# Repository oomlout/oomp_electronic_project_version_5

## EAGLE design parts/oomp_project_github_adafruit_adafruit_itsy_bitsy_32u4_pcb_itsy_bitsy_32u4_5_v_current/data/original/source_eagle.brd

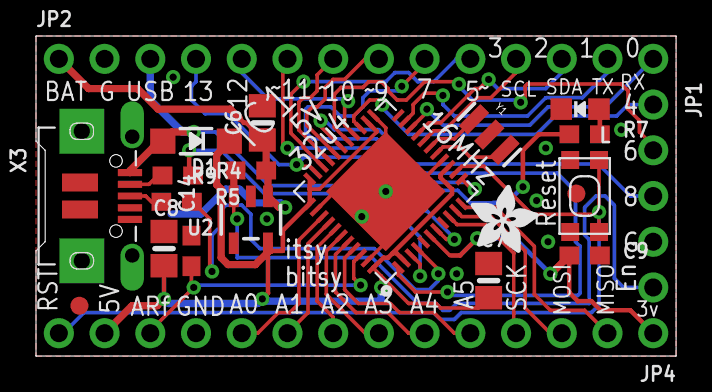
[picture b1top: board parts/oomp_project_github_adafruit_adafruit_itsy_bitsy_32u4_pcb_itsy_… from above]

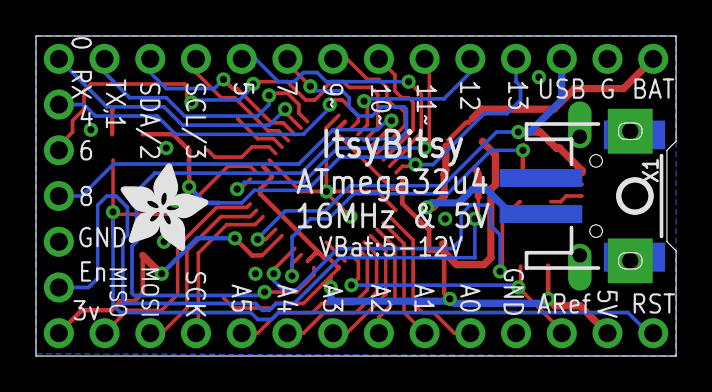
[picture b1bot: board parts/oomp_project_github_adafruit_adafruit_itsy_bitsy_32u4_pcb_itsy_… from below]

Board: 2 copper layers, 35.6 x 17.8 mm, 25 parts (3 on the bottom side), 38 nets.

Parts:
C6, C8: 10µF; 0805-NO
C7: 10uF; 0805-NO
C9, C14: 1uF; 0603-NO
D1: MBR120; SOD-123
IC1: ATMEGA32U4-MU; TQFN44_7MM
JP1: 1X05_ROUND
JP2, JP4: 1X14_ROUND70
L: RED; CHIPLED_0805_NOOUTLINE
R4, R5: 22; 0603-NO
R7: 2.2K; 0603-NO
R9: 100k; 0603-NO
SW1: SPST_TACT-KMR2; KMR2
U2: MIC5225-5.0; SOT23-5
U$4: ADAFRUIT_5MM
U$7: ADAFRUIT_3.5MM
U$10: PCBFEAT-REV-040
U$34, U$35: FIDUCIAL""; FIDUCIAL_1MM
X1: JSTPH2
X3: microUSB; 4UCONN_20329_V2
Y1: 16MHz; RESONATOR-SMD

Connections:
3.3V: C9.1, IC1.6, JP4.1
+5V: C7.1, C8.1, D1.C, IC1.2, IC1.14, IC1.24, IC1.33, IC1.34, IC1.44, JP4.13, U2.5
A0: IC1.36, JP4.10
A1: IC1.37, JP4.9
A2: IC1.38, JP4.8
A3: IC1.39, JP4.7
A4: IC1.40, JP4.6
A5: IC1.41, JP4.5
AREF: C14.1, IC1.42, JP4.12
D0: IC1.20, JP2.14
D1: IC1.21, JP2.13
D4: IC1.25, JP1.1
D5: IC1.31, JP2.10
D6: IC1.27, JP1.2
D7: IC1.1, JP2.9
D8: IC1.28, JP1.3
D9: IC1.29, JP2.8
D10: IC1.30, JP2.7
D11: IC1.12, JP2.6
D12: IC1.26, JP2.5
D13: IC1.32, JP2.4, R7.1
D+: IC1.4, R5.2
D-: IC1.3, R4.2
EN: JP1.5, R9.2, U2.3
GND: C6.2, C7.2, C8.2, C9.2, C14.2, IC1.5, IC1.15, IC1.23, IC1.35, IC1.43, JP1.4, JP2.2, JP4.11, L.C, SW1.2, SW1.4, U2.2, X1.1, X3.BASE@1, X3.BASE@2, X3.GND, X3.SPRT@1, X3.SPRT@2, X3.SPRT@3, X3.SPRT@4, Y1.2
MISO: IC1.11, JP4.2
MOSI: IC1.10, JP4.3
unnamed: L.A, R7.2
unnamed: IC1.16, Y1.3
unnamed: IC1.17, Y1.1
unnamed: R5.1, X3.D+
unnamed: R4.1, X3.D-
RST: IC1.13, JP4.14, SW1.1, SW1.3
SCK: IC1.9, JP4.4
SCL: IC1.18, JP2.11
SDA: IC1.19, JP2.12
VBAT: C6.1, JP2.1, R9.1, U2.1, X1.2
VBUS: D1.A, IC1.7, JP2.3, X3.VBUS

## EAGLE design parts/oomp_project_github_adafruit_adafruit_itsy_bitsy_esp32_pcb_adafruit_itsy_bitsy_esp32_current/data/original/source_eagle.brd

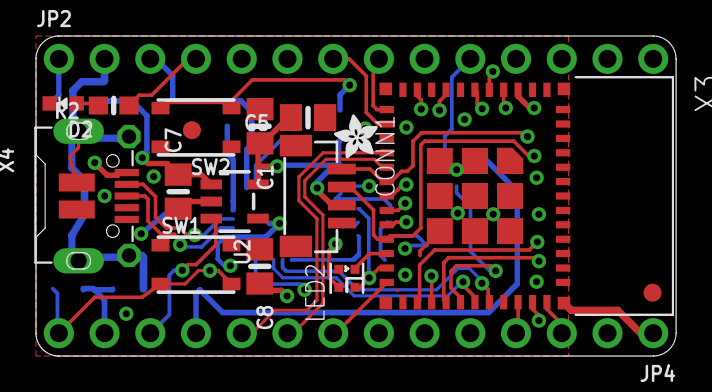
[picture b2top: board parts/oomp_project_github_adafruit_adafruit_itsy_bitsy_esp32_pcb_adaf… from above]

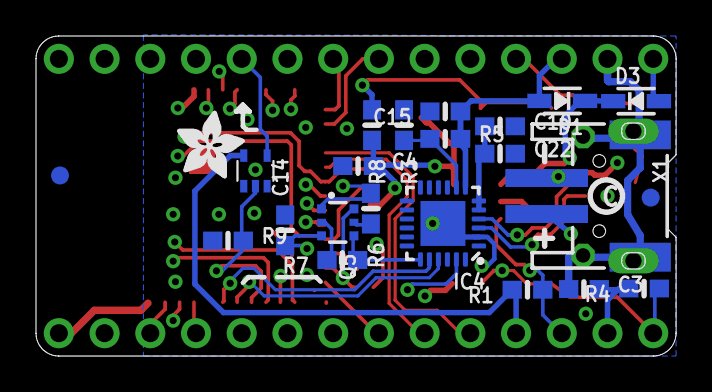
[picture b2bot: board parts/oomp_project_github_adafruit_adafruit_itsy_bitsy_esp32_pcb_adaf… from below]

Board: 4 copper layers, 35.6 x 17.8 mm, 87 parts (48 on the bottom side), 42 nets.

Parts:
C1, C5, C7, C8: 10uF; 0805-NO
C3, C4, C10, C14: 1uF; 0603-NO
C15, C22: 0.1uF; 0603-NO
CONN1: STEMMA_I2C_QTRA; JST_SH4_RA
D1, D3: BAT20J; SOD-323
D2: RED; CHIPLED_0603_NOOUTLINE
E$1: ADAFRUIT_2.5MM
E$2: ADAFRUIT_3.5MM
FID1, FID2, FID3, FID4: FIDUCIAL_1MM
IC1: 74AHCT1G125DCKR; SC70-5
IC4: CH9102F; QFN24_4MM_SMSC
JP2, JP4: 1X14_ROUND70
LED2: WS2812B_SK6805_1515; SK6805_1515
PLABEL0: PLABEL0
PLABEL1: PLABEL1
PLABEL2: PLABEL2
PLABEL3: PLABEL3
PLABEL4: PLABEL4
PLABEL5: PLABEL5
PLABEL6: PLABEL6
PLABEL7: PLABEL7
PLABEL8: PLABEL8
PLABEL9: PLABEL9
PLABEL10: PLABEL10
PLABEL11: PLABEL11
PLABEL12: PLABEL12
PLABEL13: PLABEL13
PLABEL14: PLABEL14
PLABEL15: PLABEL15
PLABEL16: PLABEL16
PLABEL17: PLABEL17
PLABEL18: PLABEL18
PLABEL19: PLABEL19
PLABEL20: PLABEL20
PLABEL21: PLABEL21
PLABEL22: PLABEL22
PLABEL23: PLABEL23
PLABEL24: PLABEL24
PLABEL25: PLABEL25
PLABEL26: PLABEL26
PLABEL27: PLABEL27
PLABEL28: PLABEL28
PLABEL29: PLABEL29
PLABEL30: PLABEL30
PLABEL31: PLABEL31
PLABEL32: PLABEL32
PLABEL33: PLABEL33
PLABEL34: PLABEL34
PLABEL35: PLABEL35
PLABEL36: PLABEL36
PLABEL37: PLABEL37
PLABEL38: PLABEL38
PLABEL39: PLABEL39
PLABEL40: PLABEL40
PLABEL41: PLABEL41
PLABEL42: PLABEL42
PLABEL43: PLABEL43
PLABEL44: PLABEL44
Q5: DUAL NPN; SOT363
R1, R2, R4, R6, R7, R8: 10K; 0603-NO
R3, R9: 47K; 0603-NO
R5: 20K; 0603-NO
SW1, SW2: KMR2; BTN_RKB2_4.6X2.8
U2: RT9080-3.3; SOT23-5
U$16: PCBFEAT-REV-040
X1: DNP; JSTPH2_BATT
X3: ESP32-PICO-MINI-02MINI; ESP32-PICO-MINI
X4: 20329; 4UCONN_20329_SLIM

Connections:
3.3V: C1.2, C3.2, C4.2, C5.2, C8.2, CONN1.2, JP4.13, R4.2, R8.2, U2.5, X3.3
3.45V: C10.1, C22.1, IC4.5, IC4.6
!RESET: C14.1, JP4.14, Q5.3, R4.1, SW1.B, SW1.B', X3.8
A0: JP4.10, X3.15
A1: JP4.9, X3.16
A2: JP4.8, X3.24
A3: JP4.7, X3.6
A4: JP4.6, X3.5
A5: JP4.5, X3.4
D5: IC1.2, R9.2, X3.29
D5_5V: IC1.4, JP2.10
D7: JP2.9, X3.27
D12: JP2.5, X3.19
D13: JP2.4, R2.1, X3.20
D14: JP2.6, X3.18
D32: JP2.8, X3.12
D33: JP2.7, X3.13
D+: IC4.3, X4.D+
D-: IC4.4, X4.D-
DTR: IC4.23, Q5.1, R6.1
EN: JP4.12, R1.1, U2.3
GND: C1.1, C3.1, C4.1, C5.1, C7.1, C8.1, C10.2, C14.2, C15.2, C22.2, CONN1.1, CONN1.MT1, CONN1.MT2, D2.C, IC1.1, IC1.3, IC4.2, IC4.THERM, JP2.2, JP4.1, LED2.4, R3.1, R9.1, SW1.A, SW1.A', SW2.A, SW2.A', U2.2, X1.1, X1.NC1, X1.NC2, X3.1, X3.2, X3.11, X3.14, X3.36, X3.37, X3.38, X3.39, X3.40, X3.41, X3.42, X3.43, X3.44, X3.45, X3.46, X3.47, X3.48, X3.49, X3.50, X3.51, X3.52, X3.53, X3.54, X3.55, X3.56, X3.57, X3.58, X3.59, X3.60, X3.61, X4.BASE@1, X4.BASE@2, X4.GND, X4.SPRT@1, X4.SPRT@2, X4.SPRT@3, X4.SPRT@4
GPIO0: LED2.1, Q5.6, X3.23
MISO: JP4.2, X3.34
MOSI: JP4.3, X3.35
unnamed: D2.A, R2.2
unnamed: Q5.5, R6.2
unnamed: Q5.2, R7.2
NEOPIX_PWR: LED2.2, X3.22
RTS: IC4.19, Q5.4, R7.1
RX: JP2.14, X3.28
RXD0: IC4.21, X3.30
SCK: JP4.4, X3.33
SCL: CONN1.4, JP2.11, X3.17
SDA: CONN1.3, JP2.12, X3.21
SW_I35: R8.1, SW2.B, SW2.B', X3.10
TX: JP2.13, X3.26
TXD0: IC4.20, X3.31
VBAT: D3.A, JP2.1, X1.2
VBUS: C15.1, D1.A, IC4.7, JP2.3, R5.2, X4.VBUS
VBUS_DET: IC4.8, R3.2, R5.1
VHI: C7.2, D1.C, D3.C, IC1.5, JP4.11, R1.2, U2.1

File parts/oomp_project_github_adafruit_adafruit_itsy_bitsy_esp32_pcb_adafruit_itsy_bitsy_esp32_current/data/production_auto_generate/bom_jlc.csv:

Comment,Designator,Footprint,LCSC Part #
,"JP2,JP4",Adafruit ItsyBitsy ESP32-import-fps:1X14_ROUND70,C2905490
,E$1,Adafruit ItsyBitsy ESP32-import-fps:ADAFRUIT_2.5MM,
,E$2,Adafruit ItsyBitsy ESP32-import-fps:ADAFRUIT_3.5MM,
,U$16,Adafruit ItsyBitsy ESP32-import-fps:PCBFEAT-REV-040,
,PLABEL0,Adafruit ItsyBitsy ESP32-import-fps:PLABEL0,
,PLABEL1,Adafruit ItsyBitsy ESP32-import-fps:PLABEL1,
,PLABEL10,Adafruit ItsyBitsy ESP32-import-fps:PLABEL10,
,PLABEL11,Adafruit ItsyBitsy ESP32-import-fps:PLABEL11,
,PLABEL12,Adafruit ItsyBitsy ESP32-import-fps:PLABEL12,
,PLABEL13,Adafruit ItsyBitsy ESP32-import-fps:PLABEL13,
,PLABEL14,Adafruit ItsyBitsy ESP32-import-fps:PLABEL14,
,PLABEL15,Adafruit ItsyBitsy ESP32-import-fps:PLABEL15,
,PLABEL16,Adafruit ItsyBitsy ESP32-import-fps:PLABEL16,
,PLABEL17,Adafruit ItsyBitsy ESP32-import-fps:PLABEL17,
,PLABEL18,Adafruit ItsyBitsy ESP32-import-fps:PLABEL18,
,PLABEL19,Adafruit ItsyBitsy ESP32-import-fps:PLABEL19,
,PLABEL2,Adafruit ItsyBitsy ESP32-import-fps:PLABEL2,
,PLABEL20,Adafruit ItsyBitsy ESP32-import-fps:PLABEL20,
,PLABEL21,Adafruit ItsyBitsy ESP32-import-fps:PLABEL21,
,PLABEL22,Adafruit ItsyBitsy ESP32-import-fps:PLABEL22,
,PLABEL23,Adafruit ItsyBitsy ESP32-import-fps:PLABEL23,
,PLABEL24,Adafruit ItsyBitsy ESP32-import-fps:PLABEL24,
,PLABEL25,Adafruit ItsyBitsy ESP32-import-fps:PLABEL25,
,PLABEL26,Adafruit ItsyBitsy ESP32-import-fps:PLABEL26,
,PLABEL27,Adafruit ItsyBitsy ESP32-import-fps:PLABEL27,
,PLABEL28,Adafruit ItsyBitsy ESP32-import-fps:PLABEL28,
,PLABEL29,Adafruit ItsyBitsy ESP32-import-fps:PLABEL29,
,PLABEL3,Adafruit ItsyBitsy ESP32-import-fps:PLABEL3,
,PLABEL30,Adafruit ItsyBitsy ESP32-import-fps:PLABEL30,
,PLABEL31,Adafruit ItsyBitsy ESP32-import-fps:PLABEL31,
,PLABEL32,Adafruit ItsyBitsy ESP32-import-fps:PLABEL32,
,PLABEL33,Adafruit ItsyBitsy ESP32-import-fps:PLABEL33,
,PLABEL34,Adafruit ItsyBitsy ESP32-import-fps:PLABEL34,
,PLABEL35,Adafruit ItsyBitsy ESP32-import-fps:PLABEL35,
,PLABEL36,Adafruit ItsyBitsy ESP32-import-fps:PLABEL36,
,PLABEL37,Adafruit ItsyBitsy ESP32-import-fps:PLABEL37,
,PLABEL38,Adafruit ItsyBitsy ESP32-import-fps:PLABEL38,
,PLABEL39,Adafruit ItsyBitsy ESP32-import-fps:PLABEL39,
,PLABEL4,Adafruit ItsyBitsy ESP32-import-fps:PLABEL4,
,PLABEL40,Adafruit ItsyBitsy ESP32-import-fps:PLABEL40,
,PLABEL41,Adafruit ItsyBitsy ESP32-import-fps:PLABEL41,
,PLABEL42,Adafruit ItsyBitsy ESP32-import-fps:PLABEL42,
,PLABEL43,Adafruit ItsyBitsy ESP32-import-fps:PLABEL43,
,PLABEL44,Adafruit ItsyBitsy ESP32-import-fps:PLABEL44,
,PLABEL5,Adafruit ItsyBitsy ESP32-import-fps:PLABEL5,
,PLABEL6,Adafruit ItsyBitsy ESP32-import-fps:PLABEL6,
,PLABEL7,Adafruit ItsyBitsy ESP32-import-fps:PLABEL7,
,PLABEL8,Adafruit ItsyBitsy ESP32-import-fps:PLABEL8,
,PLABEL9,Adafruit ItsyBitsy ESP32-import-fps:PLABEL9,
0.1uF,"C15,C22",Adafruit ItsyBitsy ESP32-import-fps:0603-NO,C14663
10K,"R1,R2,R4,R6,R7,R8",Adafruit ItsyBitsy ESP32-import-fps:0603-NO,C98220
10uF,"C1,C5,C7,C8",Adafruit ItsyBitsy ESP32-import-fps:0805-NO,
1uF,"C3,C4,C10,C14",Adafruit ItsyBitsy ESP32-import-fps:0603-NO,C5673
20329,X4,Adafruit ItsyBitsy ESP32-import-fps:4UCONN_20329_SLIM,
20K,R5,Adafruit ItsyBitsy ESP32-import-fps:0603-NO,
47K,"R3,R9",Adafruit ItsyBitsy ESP32-import-fps:0603-NO,C2907042
74AHCT1G125DCKR,IC1,Adafruit ItsyBitsy ESP32-import-fps:SC70-5,
BAT20J,"D1,D3",Adafruit ItsyBitsy ESP32-import-fps:SOD-323,
CH9102F,IC4,Adafruit ItsyBitsy ESP32-import-fps:QFN24_4MM_SMSC,
DNP,X1,Adafruit ItsyBitsy ESP32-import-fps:JSTPH2_BATT,
DUAL NPN,Q5,Adafruit ItsyBitsy ESP32-import-fps:SOT363,
ESP32-PICO-MINI-02MINI,X3,Adafruit ItsyBitsy ESP32-import-fps:ESP32-PICO-MINI,
KMR2,"SW1,SW2",Adafruit ItsyBitsy ESP32-import-fps:BTN_RKB2_4.6X2.8,
RED,D2,Adafruit ItsyBitsy ESP32-import-fps:CHIPLED_0603_NOOUTLINE,
RT9080-3.3,U2,Adafruit ItsyBitsy ESP32-import-fps:SOT23-5,
STEMMA_I2C_QTRA,CONN1,Adafruit ItsyBitsy ESP32-import-fps:JST_SH4_RA,
WS2812B_SK6805_1515,LED2,Adafruit ItsyBitsy ESP32-import-fps:SK6805_1515,

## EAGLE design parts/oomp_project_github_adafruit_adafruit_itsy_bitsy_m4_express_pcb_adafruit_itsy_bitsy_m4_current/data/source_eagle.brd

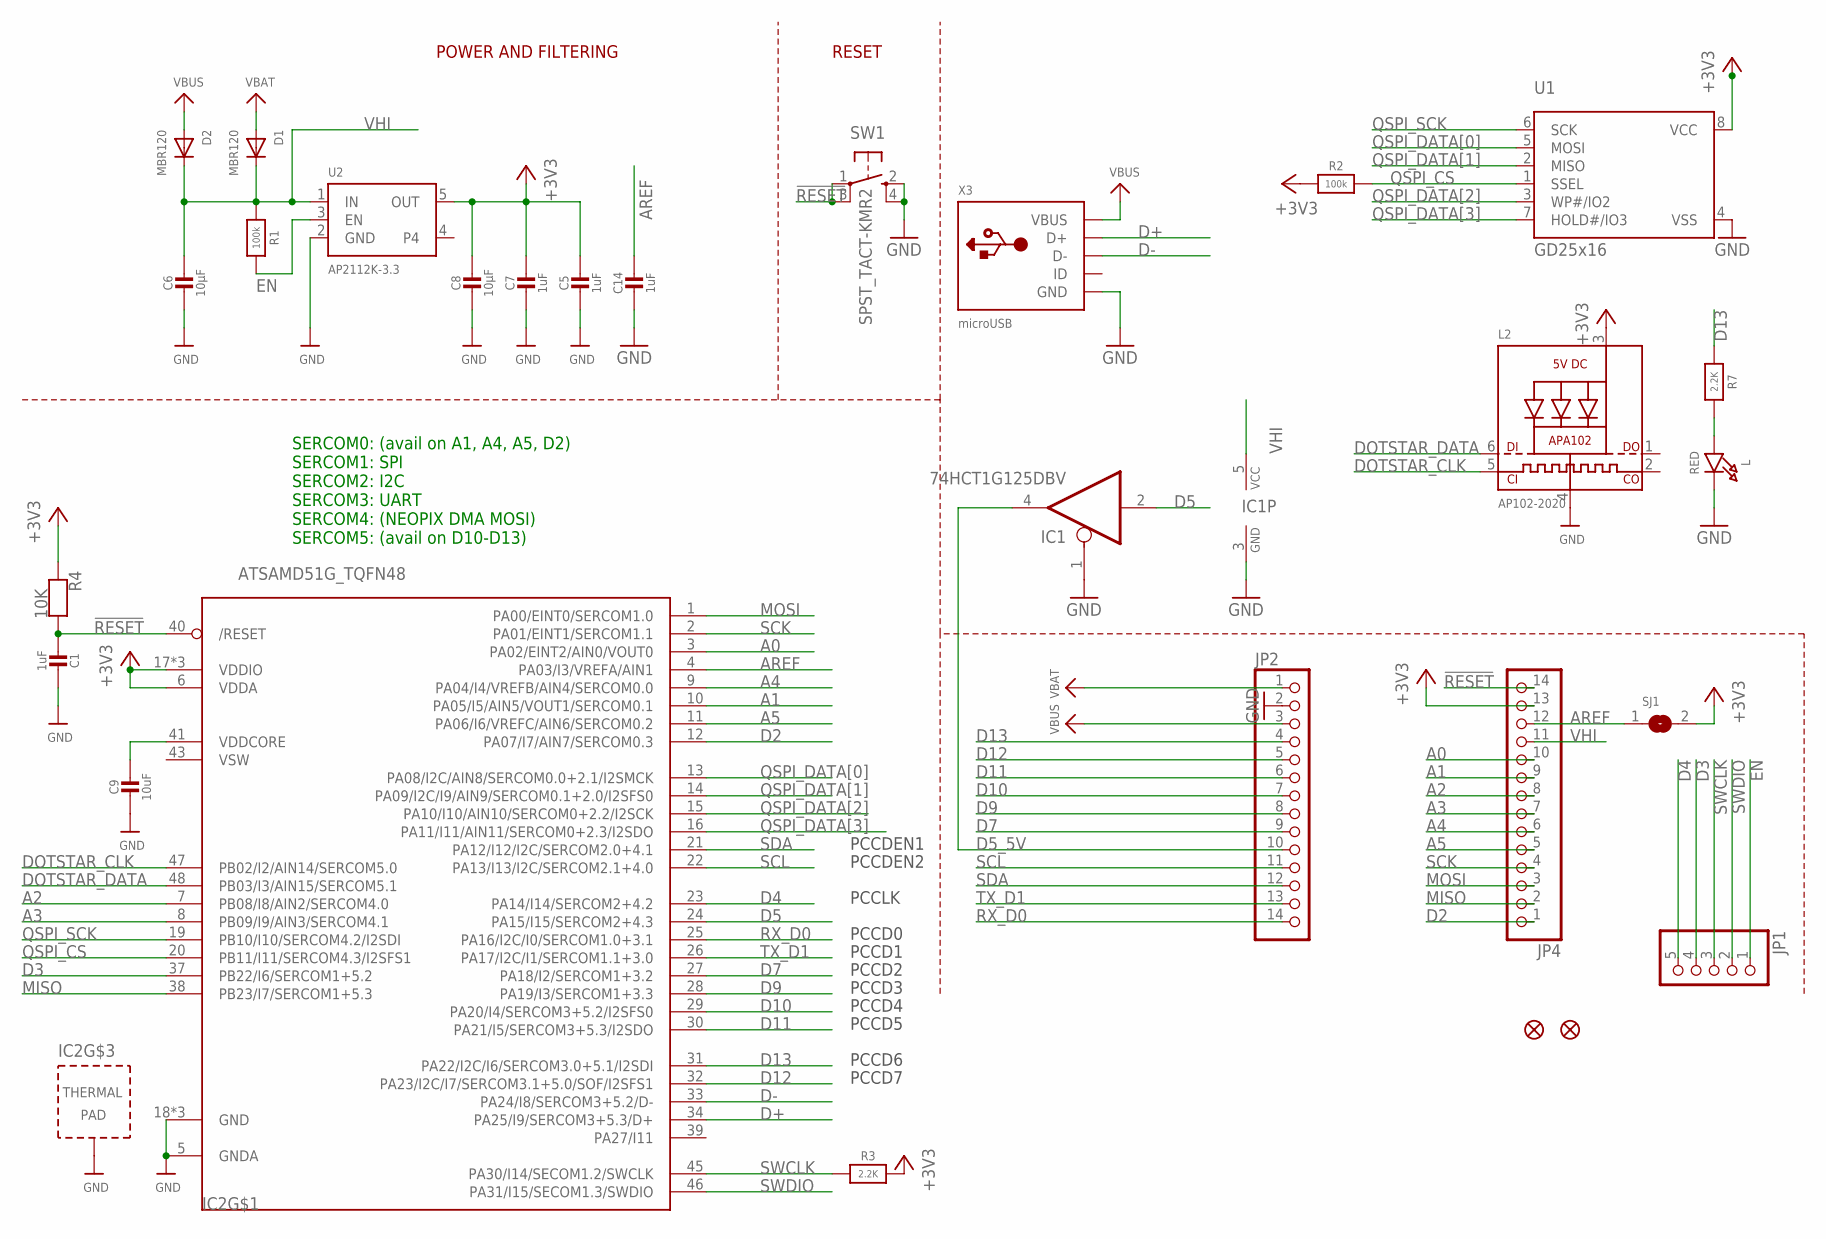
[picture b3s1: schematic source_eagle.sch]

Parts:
C1: 1uF; _0603MP
C5, C7, C14: 1uF; 0603-NO
C6, C8: 10µF; 0805-NO
C9: 10uF; _0805MP
D1, D2: MBR120; SOD-123FL
IC1: 74HCT1G125DBV; SOT23-5
IC2: ATSAMD51G_TQFN48; TQFN48_7MM
JP1: HEADER-1X570MIL; 1X05_ROUND_70
JP2, JP4: HEADER-1X14; 1X14_ROUND70
L: RED; CHIPLED_0603_NOOUTLINE
L2: AP102-2020; APA102_2020
R1, R2: 100k; 0603-NO
R3: 2.2K; _0603MP
R4: 10K; _0603MP
R7: 2.2K; 0603-NO
SJ1: SOLDERJUMPERCLOSED; SOLDERJUMPER_CLOSEDWIRE
SW1: SPST_TACT-KMR2; KMR2
U1: GD25x16; USON8
U2: AP2112K-3.3; SOT23-5
U$34, U$35: FIDUCIAL_1MM
X3: microUSB; 4UCONN_20329_V2

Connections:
!RESET: C1.2, IC2.40 (/RESET), JP4.14, R4.2, SW1.1, SW1.3 (P1)
+3V3: C5.1, C7.1, C8.1, IC2.6 (VDDA), IC2.17 (VDDIO), IC2.36 (VDDIO), IC2.44 (VDDIO), JP4.13, L2.3 (VDD), R2.1, R3.2, R4.1, SJ1.2, U1.8 (VCC), U2.5 (OUT)
A0: IC2.3 (PA02/EINT2/AIN0/VOUT0), JP4.10
A1: IC2.10 (PA05/I5/AIN5/VOUT1/SERCOM0.1), JP4.9
A2: IC2.7 (PB08/I8/AIN2/SERCOM4.0), JP4.8
A3: IC2.8 (PB09/I9/AIN3/SERCOM4.1), JP4.7
A4: IC2.9 (PA04/I4/VREFB/AIN4/SERCOM0.0), JP4.6
A5: IC2.11 (PA06/I6/VREFC/AIN6/SERCOM0.2), JP4.5
AREF: C14.1, IC2.4 (PA03/I3/VREFA/AIN1), JP4.12, SJ1.1
D2: IC2.12 (PA07/I7/AIN7/SERCOM0.3), JP4.1
D3: IC2.37 (PB22/I6/SERCOM1+5.2), JP1.4
D4: IC2.23 (PA14/I14/SERCOM2+4.2), JP1.5
D5: IC1.2 (I), IC2.24 (PA15/I15/SERCOM2+4.3)
D5_5V: IC1.4 (O), JP2.10
D7: IC2.27 (PA18/I2/SERCOM1+3.2), JP2.9
D9: IC2.28 (PA19/I3/SERCOM1+3.3), JP2.8
D10: IC2.29 (PA20/I4/SERCOM3+5.2/I2SFS0), JP2.7
D11: IC2.30 (PA21/I5/SERCOM3+5.3/I2SDO), JP2.6
D12: IC2.32 (PA23/I2C/I7/SERCOM3.1+5.0/SOF/I2SFS1), JP2.5
D13: IC2.31 (PA22/I2C/I6/SERCOM3.0+5.1/I2SDI), JP2.4, R7.1
D+: IC2.34 (PA25/I9/SERCOM3+5.3/D+), X3.D+
D-: IC2.33 (PA24/I8/SERCOM3+5.2/D-), X3.D-
DOTSTAR_CLK: IC2.47 (PB02/I2/AIN14/SERCOM5.0), L2.5 (CKI)
DOTSTAR_DATA: IC2.48 (PB03/I3/AIN15/SERCOM5.1), L2.6 (DI)
EN: JP1.1, R1.2, U2.3 (EN)
GND: C1.1, C5.2, C6.2, C7.2, C8.2, C9.2, C14.2, IC1.1 (OE), IC1.3 (GND), IC2.5 (GNDA), IC2.18 (GND), IC2.35 (GND), IC2.42 (GND), IC2.THERMAL (TP), JP2.2, L.C, L2.4 (GND), SW1.2 (S), SW1.4 (S1), U1.4 (VSS), U2.2 (GND), X3.BASE@1 (GND), X3.BASE@2 (GND), X3.GND, X3.SPRT@1 (GND), X3.SPRT@2 (GND), X3.SPRT@3 (GND), X3.SPRT@4 (GND)
MISO: IC2.38 (PB23/I7/SERCOM1+5.3), JP4.2
MOSI: IC2.1 (PA00/EINT0/SERCOM1.0), JP4.3
unnamed: L.A, R7.2
QSPI_CS: IC2.20 (PB11/I11/SERCOM4.3/I2SFS1), R2.2, U1.1 (SSEL)
QSPI_DATA[0]: IC2.13 (PA08/I2C/AIN8/SERCOM0.0+2.1/I2SMCK), U1.5 (MOSI)
QSPI_DATA[1]: IC2.14 (PA09/I2C/I9/AIN9/SERCOM0.1+2.0/I2SFS0), U1.2 (MISO)
QSPI_DATA[2]: IC2.15 (PA10/I10/AIN10/SERCOM0+2.2/I2SCK), U1.3 (WP#/IO2)
QSPI_DATA[3]: IC2.16 (PA11/I11/AIN11/SERCOM0+2.3/I2SDO), U1.7 (HOLD#/IO3)
QSPI_SCK: IC2.19 (PB10/I10/SERCOM4.2/I2SDI), U1.6 (SCK)
RX_D0: IC2.25 (PA16/I2C/I0/SERCOM1.0+3.1), JP2.14
SCK: IC2.2 (PA01/EINT1/SERCOM1.1), JP4.4
SCL: IC2.22 (PA13/I13/I2C/SERCOM2.1+4.0), JP2.11
SDA: IC2.21 (PA12/I12/I2C/SERCOM2.0+4.1), JP2.12
SWCLK: IC2.45 (PA30/I14/SECOM1.2/SWCLK), JP1.3, R3.1
SWDIO: IC2.46 (PA31/I15/SECOM1.3/SWDIO), JP1.2
TX_D1: IC2.26 (PA17/I2C/I1/SERCOM1.1+3.0), JP2.13
VBAT: D1.A, JP2.1
VBUS: D2.A, JP2.3, X3.VBUS
VDDCORE: C9.1, IC2.41 (VDDCORE)
VHI: C6.1, D1.C, D2.C, IC1.5 (VCC), JP4.11, R1.1, U2.1 (IN)
VSW: IC2.43 (VSW)

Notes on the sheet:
POWER AND FILTERING
RESET
SERCOM0: (avail on A1, A4, A5, D2) SERCOM1: SPI SERCOM2: I2C SERCOM3: UART SERCOM4: (NEOPIX DMA MOSI) SERCOM5: (avail on D10-D13)
PCCDEN1
PCCDEN2
PCCD0
PCCD1
PCCD2
PCCD3
PCCD4
PCCD5
PCCD6
PCCD7
PCCLK

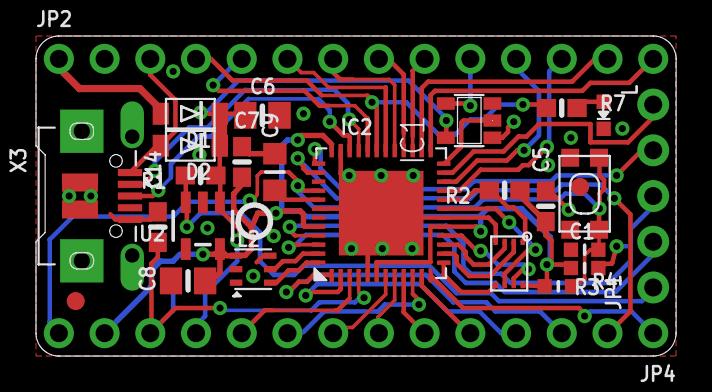
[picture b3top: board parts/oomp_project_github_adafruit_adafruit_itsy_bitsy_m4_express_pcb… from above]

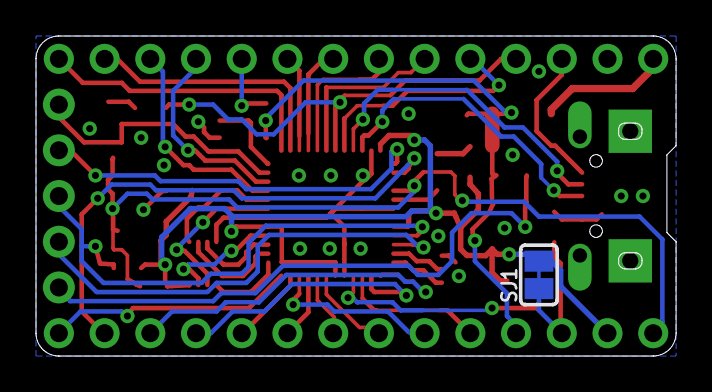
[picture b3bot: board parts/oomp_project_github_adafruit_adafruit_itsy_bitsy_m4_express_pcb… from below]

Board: 2 copper layers, 35.6 x 17.8 mm, 31 parts (2 on the bottom side), 46 nets.

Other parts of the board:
U$4: ITSYM4_TOP
U$5: ITSYM4_BOT
U$6: PCBFEAT-REV-040

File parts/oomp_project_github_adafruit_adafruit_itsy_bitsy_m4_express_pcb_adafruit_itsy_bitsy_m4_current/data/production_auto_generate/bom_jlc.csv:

Comment,Designator,Footprint,LCSC Part #
,JP1,Adafruit ItsyBitsy M4-import-fps:1X05_ROUND_70,C42431835
,"JP2,JP4",Adafruit ItsyBitsy M4-import-fps:1X14_ROUND70,C2905490
,U$5,Adafruit ItsyBitsy M4-import-fps:ITSYM4_BOT,
,U$4,Adafruit ItsyBitsy M4-import-fps:ITSYM4_TOP,
,U$6,Adafruit ItsyBitsy M4-import-fps:PCBFEAT-REV-040,
100k,"R1,R2",Adafruit ItsyBitsy M4-import-fps:0603-NO,C25803
10K,R4,Adafruit ItsyBitsy M4-import-fps:_0603MP,C98220
10uF,C9,Adafruit ItsyBitsy M4-import-fps:_0805MP,
10µF,"C6,C8",Adafruit ItsyBitsy M4-import-fps:0805-NO,
1uF,"C5,C7,C14",Adafruit ItsyBitsy M4-import-fps:0603-NO,C5673
1uF,C1,Adafruit ItsyBitsy M4-import-fps:_0603MP,C5673
2.2K,R7,Adafruit ItsyBitsy M4-import-fps:0603-NO,C4190
2.2K,R3,Adafruit ItsyBitsy M4-import-fps:_0603MP,C4190
74HCT1G125DBV,IC1,Adafruit ItsyBitsy M4-import-fps:SOT23-5,
AP102-2020,L2,Adafruit ItsyBitsy M4-import-fps:APA102_2020,
AP2112K-3.3,U2,Adafruit ItsyBitsy M4-import-fps:SOT23-5,
ATSAMD51G_TQFN48,IC2,Adafruit ItsyBitsy M4-import-fps:TQFN48_7MM,
FIDUCIAL_1MM,"U$34,U$35",Adafruit ItsyBitsy M4-import-fps:FIDUCIAL_1MM,
GD25x16,U1,Adafruit ItsyBitsy M4-import-fps:USON8,
MBR120,"D1,D2",Adafruit ItsyBitsy M4-import-fps:SOD-123FL,
microUSB,X3,Adafruit ItsyBitsy M4-import-fps:4UCONN_20329_V2,
RED,L0,Adafruit ItsyBitsy M4-import-fps:CHIPLED_0603_NOOUTLINE,
SPST_TACT-KMR2,SW1,Adafruit ItsyBitsy M4-import-fps:KMR2,

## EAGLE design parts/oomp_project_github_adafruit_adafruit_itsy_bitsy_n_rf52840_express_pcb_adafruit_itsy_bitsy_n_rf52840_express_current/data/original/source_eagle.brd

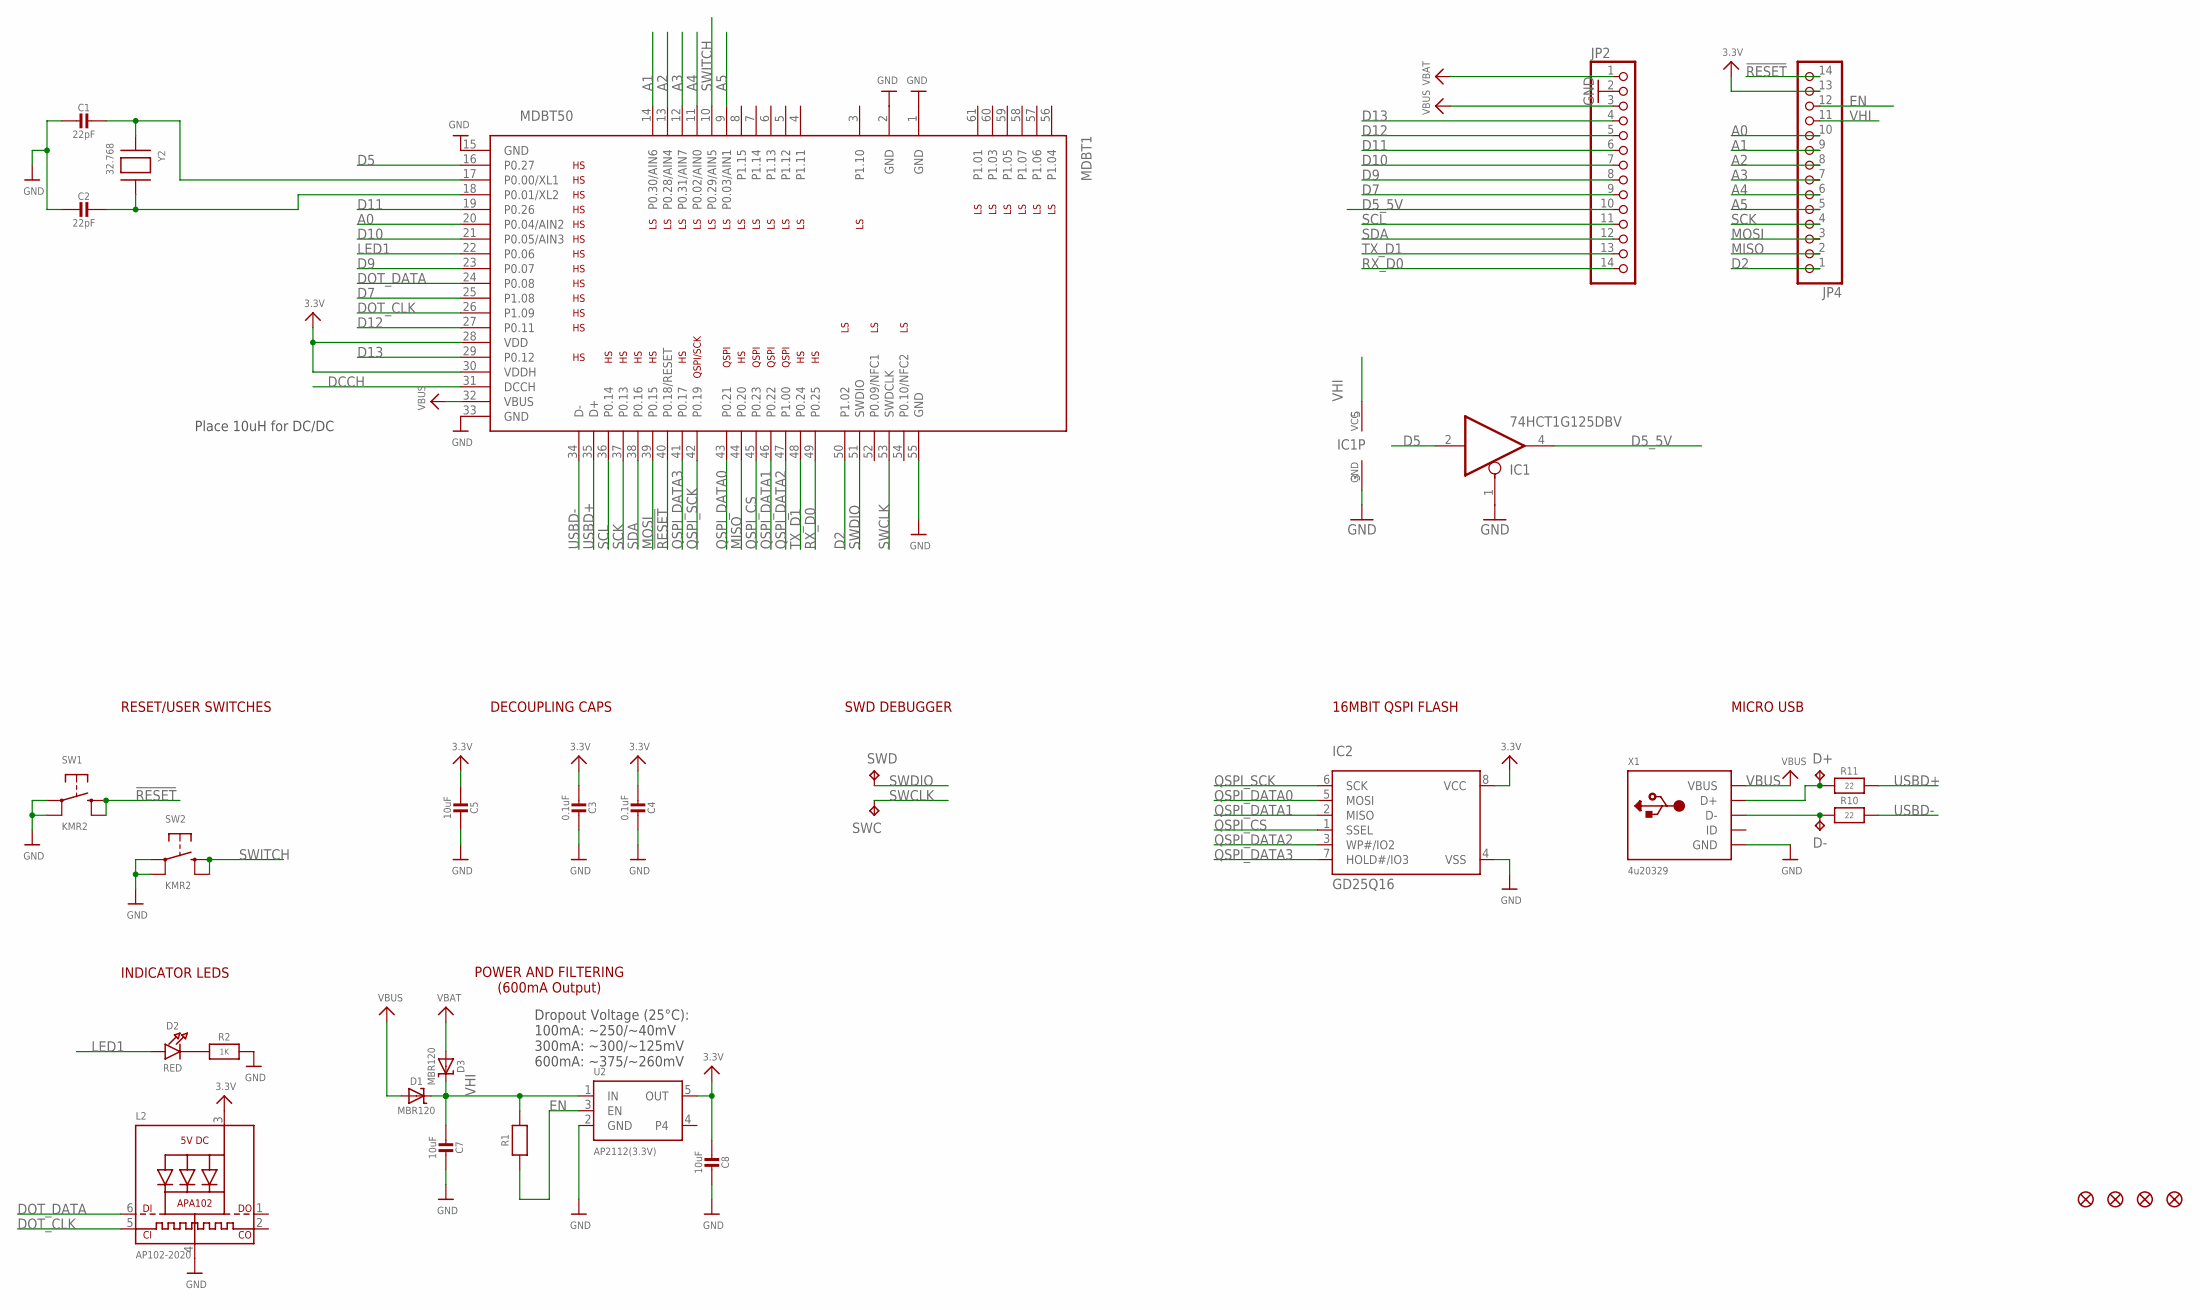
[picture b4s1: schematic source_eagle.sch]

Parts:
C1, C2: 22pF; _0603MP
C3, C4: 0.1uF; 0603-NO
C5, C7, C8: 10uF; 0805-NO
D1, D3: MBR120; SOD-123
D2: RED; CHIPLED_0805_NOOUTLINE
D+: TPTP10R; TP10R
D-: TPTP10R; TP10R
FID1, FID2, FID3, FID4: FIDUCIAL_1MM
IC1: 74HCT1G125DBV; SOT23-5
IC2: GD25Q16; USON8
JP2, JP4: HEADER-1X14; 1X14_ROUND70
L2: AP102-2020; APA102_2020
MDBT1: MDBT50
R1: 10K; 0603-NO
R2: 1K; 0603-NO
R10, R11: 22; 0603-NO
SW1, SW2: KMR2; BTN_KMR2_4.6X2.8
SWC: TPTP13R; TP13R
SWD: TPTP13R; TP13R
U2: AP2112(3.3V); SOT23-5
X1: 4u20329; 4UCONN_20329_V2
Y2: 32.768; XTAL3215

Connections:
3.3V: C3.2, C4.2, C5.2, C8.2, IC2.8 (VCC), JP4.13, L2.3 (VDD), MDBT1.28 (VDD), MDBT1.30 (VDDH), U2.5 (OUT)
!RESET: JP4.14, MDBT1.40 (P0.18/RESET), SW1.B (S), SW1.B' (S1)
A0: JP4.10, MDBT1.20 (P0.04/AIN2)
A1: JP4.9, MDBT1.14 (P0.30/AIN6)
A2: JP4.8, MDBT1.13 (P0.28/AIN4)
A3: JP4.7, MDBT1.12 (P0.31/AIN7)
A4: JP4.6, MDBT1.11 (P0.02/AIN0)
A5: JP4.5, MDBT1.9 (P0.03/AIN1)
D2: JP4.1, MDBT1.50 (P1.02)
D5: IC1.2 (I), MDBT1.16 (P0.27)
D5_5V: IC1.4 (O), JP2.10
D7: JP2.9, MDBT1.25 (P1.08)
D9: JP2.8, MDBT1.23 (P0.07)
D10: JP2.7, MDBT1.21 (P0.05/AIN3)
D11: JP2.6, MDBT1.19 (P0.26)
D12: JP2.5, MDBT1.27 (P0.11)
D13: JP2.4, MDBT1.29 (P0.12)
D+: D+.TP, R11.1, X1.D+
D-: D-.TP, R10.1, X1.D-
DCCH: MDBT1.31 (DCCH)
DOT_CLK: L2.5 (CKI), MDBT1.26 (P1.09)
DOT_DATA: L2.6 (DI), MDBT1.24 (P0.08)
EN: JP4.12, R1.1, U2.3 (EN)
GND: C1.2, C2.2, C3.1, C4.1, C5.1, C7.1, C8.1, IC1.1 (OE), IC1.3 (GND), IC2.4 (VSS), JP2.2, L2.4 (GND), MDBT1.1 (GND), MDBT1.2 (GND), MDBT1.15 (GND), MDBT1.33 (GND), MDBT1.55 (GND), R2.2, SW1.A, SW1.A' (P1), SW2.A, SW2.A' (P1), U2.2 (GND), X1.BASE@1 (GND), X1.BASE@2 (GND), X1.GND, X1.SPRT@1 (GND), X1.SPRT@2 (GND), X1.SPRT@3 (GND), X1.SPRT@4 (GND)
LED1: D2.A, MDBT1.22 (P0.06)
MISO: JP4.2, MDBT1.44 (P0.20)
MOSI: JP4.3, MDBT1.39 (P0.15)
unnamed: D2.C, R2.1
unnamed: C1.1, MDBT1.17 (P0.00/XL1), Y2.P$1
unnamed: C2.1, MDBT1.18 (P0.01/XL2), Y2.P$2
QSPI_CS: IC2.1 (SSEL), MDBT1.45 (P0.23)
QSPI_DATA0: IC2.5 (MOSI), MDBT1.43 (P0.21)
QSPI_DATA1: IC2.2 (MISO), MDBT1.46 (P0.22)
QSPI_DATA2: IC2.3 (WP#/IO2), MDBT1.47 (P1.00)
QSPI_DATA3: IC2.7 (HOLD#/IO3), MDBT1.41 (P0.17)
QSPI_SCK: IC2.6 (SCK), MDBT1.42 (P0.19)
RX_D0: JP2.14, MDBT1.49 (P0.25)
SCK: JP4.4, MDBT1.37 (P0.13)
SCL: JP2.11, MDBT1.36 (P0.14)
SDA: JP2.12, MDBT1.38 (P0.16)
SWCLK: MDBT1.53 (SWDCLK), SWC.TP
SWDIO: MDBT1.51 (SWDIO), SWD.TP
SWITCH: MDBT1.10 (P0.29/AIN5), SW2.B (S), SW2.B' (S1)
TX_D1: JP2.13, MDBT1.48 (P0.24)
USBD+: MDBT1.35 (D+), R11.2
USBD-: MDBT1.34 (D-), R10.2
VBAT: D3.A, JP2.1
VBUS: D1.A, JP2.3, MDBT1.32 (VBUS), X1.VBUS
VHI: C7.2, D1.C, D3.C, IC1.5 (VCC), JP4.11, R1.2, U2.1 (IN)

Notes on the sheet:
POWER AND FILTERING (600mA Output)
Dropout Voltage (25°C): 100mA: ~250/~40mV 300mA: ~300/~125mV 600mA: ~375/~260mV
INDICATOR LEDS
RESET/USER SWITCHES
DECOUPLING CAPS
SWD DEBUGGER
16MBIT QSPI FLASH
MICRO USB
Place 10uH for DC/DC

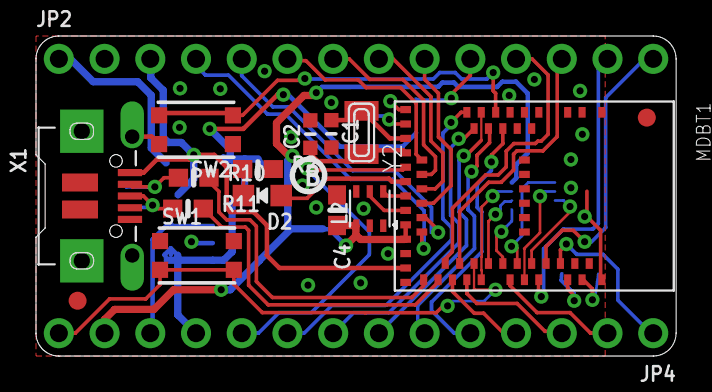
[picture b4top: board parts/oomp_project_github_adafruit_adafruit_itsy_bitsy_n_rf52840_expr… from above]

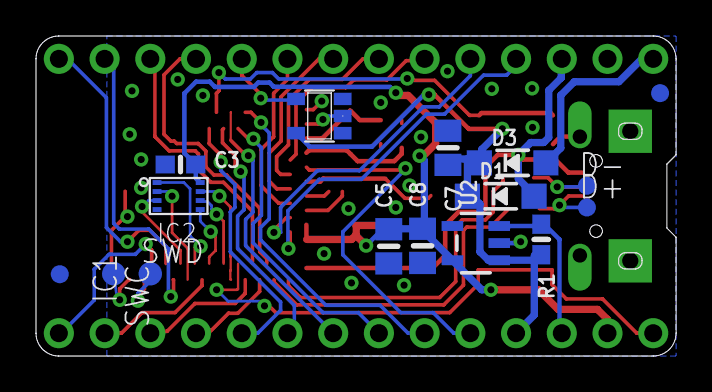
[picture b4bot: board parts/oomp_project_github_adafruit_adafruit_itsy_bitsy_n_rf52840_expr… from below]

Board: 2 copper layers, 35.6 x 17.8 mm, 36 parts (17 on the bottom side), 48 nets.

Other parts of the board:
U$12: ITSYNRF52840_TOP
U$14: ITSYNRF52840_BOT
U$15: PCBFEAT-REV-040

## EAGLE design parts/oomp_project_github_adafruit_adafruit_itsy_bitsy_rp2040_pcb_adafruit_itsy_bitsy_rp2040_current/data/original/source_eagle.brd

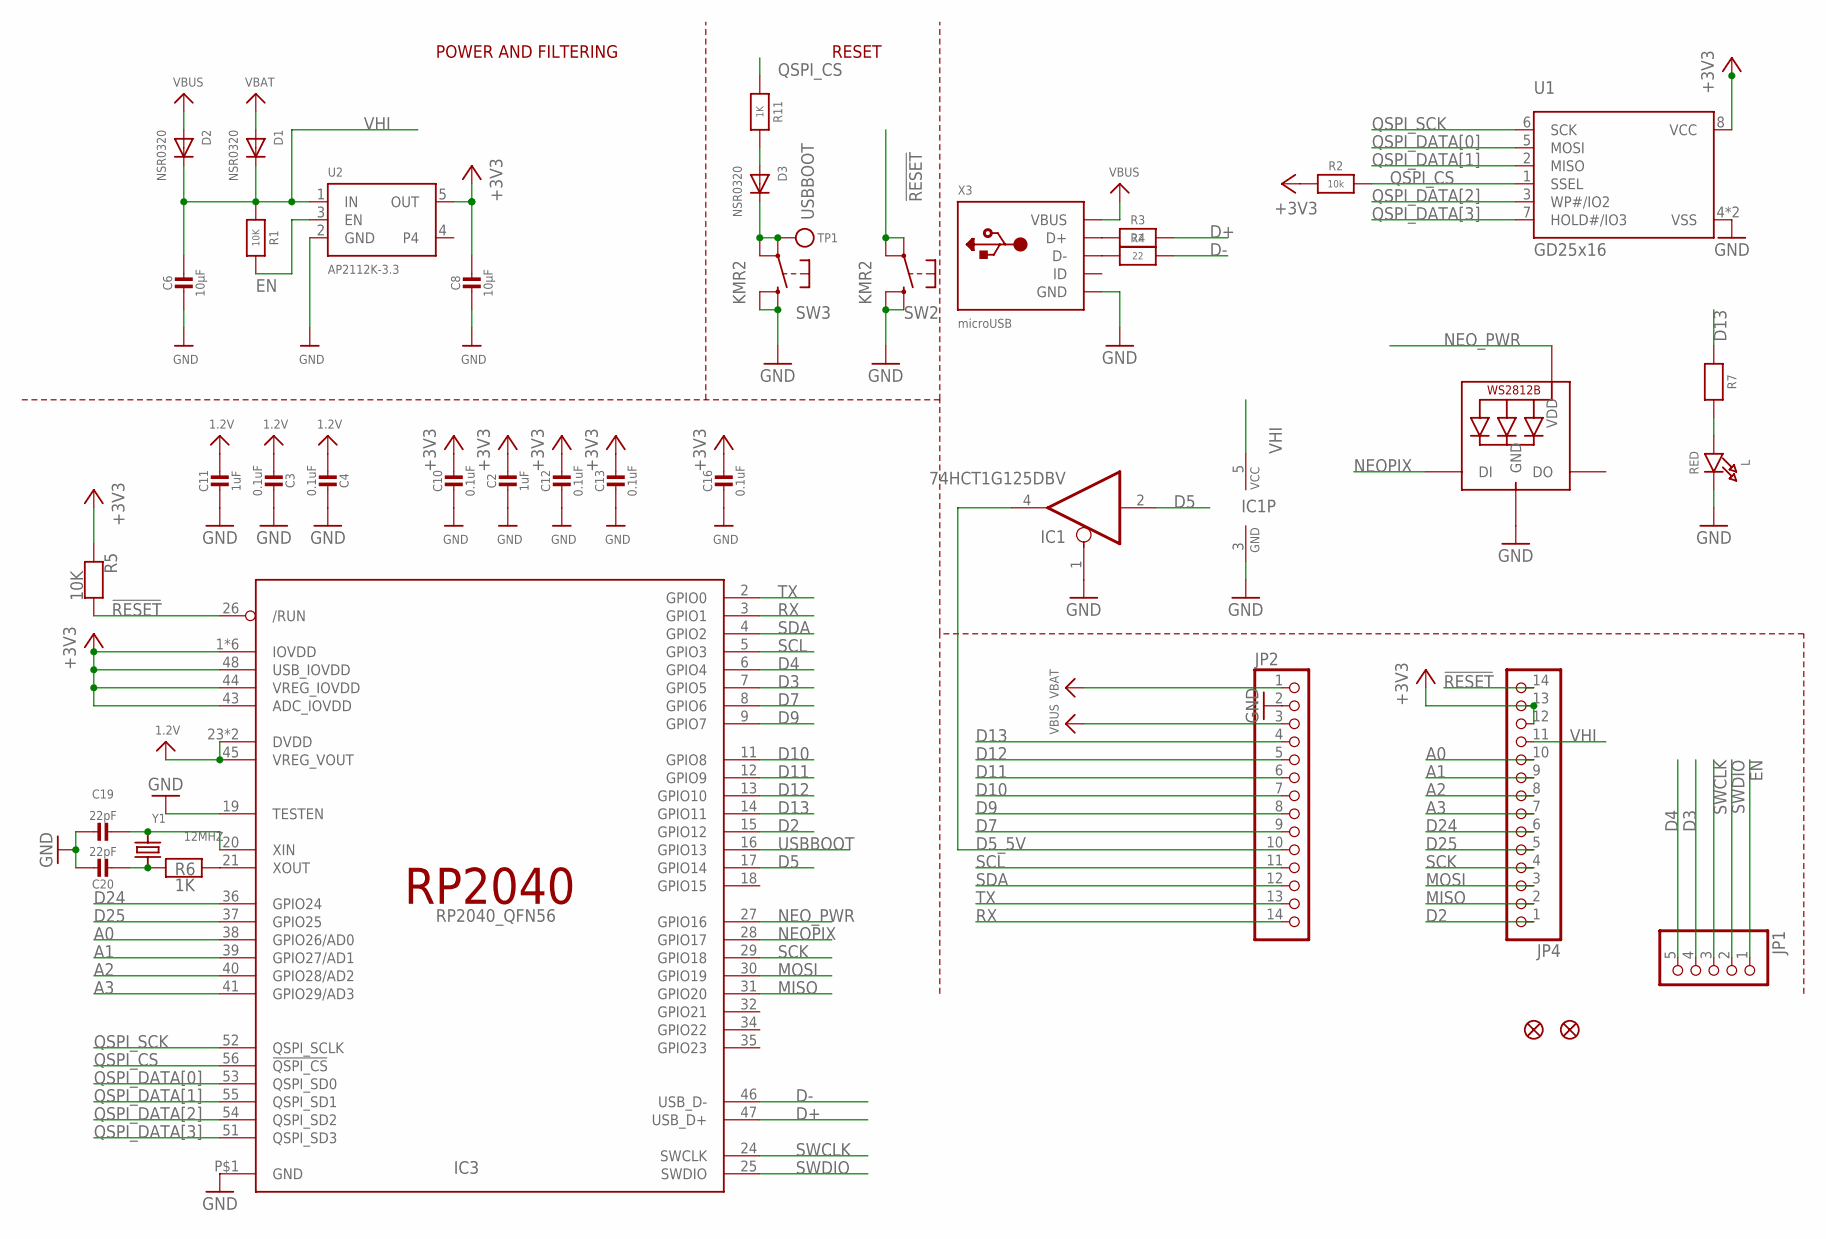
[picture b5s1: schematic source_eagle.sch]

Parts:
C2, C11: 1uF; _0603MP
C3, C4, C10, C12, C13, C16: 0.1uF; _0402NO
C6, C8: 10µF; 0805-NO
C19, C20: 22pF; _0402NO
D1, D2, D3: NSR0320; SOD-323F
IC1: 74HCT1G125DBV; SC70-5
IC3: RP2040_QFN56; QFN56_7MM_REDUCEDEPAD
JP1: HEADER-1X570MIL; 1X05_ROUND_70
JP2, JP4: HEADER-1X14; 1X14_ROUND70
L: RED; CHIPLED_0603_NOOUTLINE
LED1: WS2812B_SK6805_1515; SK6805_1515
R1, R5: 10K; _0402NO
R2: 10k; _0402NO
R3, R4: 22; _0402NO
R6, R7, R11: 1K; _0402NO
SW2, SW3: KMR2; BTN_KMR2_4.6X2.8
TP1: TESTPOINTROUND1.5MMNO; TESTPOINT_ROUND_1.5MM_NO
U1: GD25x16; USON8_4X4
U2: AP2112K-3.3; SOT23-5
U$34, U$35: FIDUCIAL_1MM
X3: microUSB; 4UCONN_20329_NARROW
Y1: 12MHZ; CRYSTAL_2.5X2

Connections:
1.2V: C3.2, C4.2, C11.1, IC3.23 (DVDD), IC3.45 (VREG_VOUT), IC3.50 (DVDD)
!RESET: IC3.26 (/RUN), JP4.14, R5.2, SW2.A, SW2.A' (P1)
+3V3: C2.1, C8.1, C10.1, C12.1, C13.1, C16.1, IC3.1 (IOVDD), IC3.10 (IOVDD), IC3.22 (IOVDD), IC3.33 (IOVDD), IC3.42 (IOVDD), IC3.43 (ADC_IOVDD), IC3.44 (VREG_IOVDD), IC3.48 (USB_IOVDD), IC3.49 (IOVDD), JP4.12, JP4.13, R2.1, R5.1, U1.8 (VCC), U2.5 (OUT)
A0: IC3.38 (GPIO26/AD0), JP4.10
A1: IC3.39 (GPIO27/AD1), JP4.9
A2: IC3.40 (GPIO28/AD2), JP4.8
A3: IC3.41 (GPIO29/AD3), JP4.7
D2: IC3.15 (GPIO12), JP4.1
D3: IC3.7 (GPIO5), JP1.4
D4: IC3.6 (GPIO4), JP1.5
D5: IC1.2 (I), IC3.17 (GPIO14)
D5_5V: IC1.4 (O), JP2.10
D7: IC3.8 (GPIO6), JP2.9
D9: IC3.9 (GPIO7), JP2.8
D10: IC3.11 (GPIO8), JP2.7
D11: IC3.12 (GPIO9), JP2.6
D12: IC3.13 (GPIO10), JP2.5
D13: IC3.14 (GPIO11), JP2.4, R7.1
D24: IC3.36 (GPIO24), JP4.6
D25: IC3.37 (GPIO25), JP4.5
D+: IC3.47 (USB_D+), R3.2
D-: IC3.46 (USB_D-), R4.2
EN: JP1.1, R1.2, U2.3 (EN)
GND: C2.2, C3.1, C4.1, C6.2, C8.2, C10.2, C11.2, C12.2, C13.2, C16.2, C19.1, C20.1, IC1.1 (OE), IC1.3 (GND), IC3.19 (TESTEN), IC3.P$1 (GND), JP2.2, L.C, LED1.4 (GND), SW2.B (S), SW2.B' (S1), SW3.B (S), SW3.B' (S1), U1.4 (VSS), U1.PAD (VSS), U2.2 (GND), X3.BASE@1 (GND), X3.BASE@2 (GND), X3.GND, X3.SPRT@1 (GND), X3.SPRT@2 (GND), X3.SPRT@3 (GND), X3.SPRT@4 (GND)
MISO: IC3.31 (GPIO20), JP4.2
MOSI: IC3.30 (GPIO19), JP4.3
unnamed: R3.1, X3.D+
unnamed: L.A, R7.2
unnamed: R4.1, X3.D-
unnamed: D3.A, R11.2
unnamed: C19.2, IC3.20 (XIN), Y1.3 (2)
unnamed: C20.2, R6.1, Y1.1
unnamed: IC3.21 (XOUT), R6.2
NEOPIX: IC3.28 (GPIO17), LED1.1 (DI)
NEO_PWR: IC3.27 (GPIO16), LED1.2 (VDD)
QSPI_CS: IC3.56 (!QSPI_CS), R2.2, R11.1, U1.1 (SSEL)
QSPI_DATA[0]: IC3.53 (QSPI_SD0), U1.5 (MOSI)
QSPI_DATA[1]: IC3.55 (QSPI_SD1), U1.2 (MISO)
QSPI_DATA[2]: IC3.54 (QSPI_SD2), U1.3 (WP#/IO2)
QSPI_DATA[3]: IC3.51 (QSPI_SD3), U1.7 (HOLD#/IO3)
QSPI_SCK: IC3.52 (QSPI_SCLK), U1.6 (SCK)
RX: IC3.3 (GPIO1), JP2.14
SCK: IC3.29 (GPIO18), JP4.4
SCL: IC3.5 (GPIO3), JP2.11
SDA: IC3.4 (GPIO2), JP2.12
SWCLK: IC3.24 (SWCLK), JP1.3
SWDIO: IC3.25 (SWDIO), JP1.2
TX: IC3.2 (GPIO0), JP2.13
USBBOOT: D3.C, IC3.16 (GPIO13), SW3.A, SW3.A' (P1), TP1.P$1
VBAT: D1.A, JP2.1
VBUS: D2.A, JP2.3, X3.VBUS
VHI: C6.1, D1.C, D2.C, IC1.5 (VCC), JP4.11, R1.1, U2.1 (IN)

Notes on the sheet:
POWER AND FILTERING
RESET

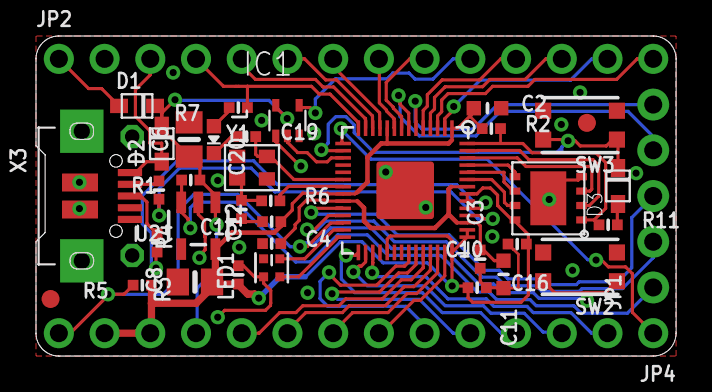
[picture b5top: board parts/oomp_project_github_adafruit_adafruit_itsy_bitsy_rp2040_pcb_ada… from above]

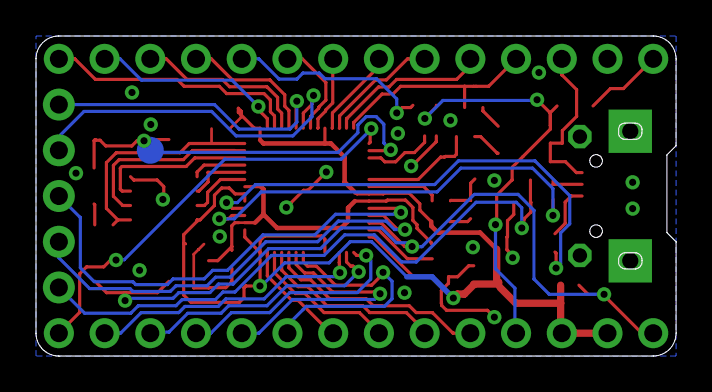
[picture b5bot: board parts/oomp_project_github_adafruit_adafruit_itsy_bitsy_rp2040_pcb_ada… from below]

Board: 2 copper layers, 35.6 x 17.8 mm, 41 parts (2 on the bottom side), 52 nets.

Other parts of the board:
U$4: ITSY2040_TOP
U$5: ITSY2040_BOT

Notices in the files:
parts and their libraries:
microbuilder: This work is placed in the public domain, and may be freely used for commercial and non-commercial work with the following conditions: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
SparkFun: Licensing: CC v3.0 Share-Alike You are welcome to use this library for commercial purposes.
